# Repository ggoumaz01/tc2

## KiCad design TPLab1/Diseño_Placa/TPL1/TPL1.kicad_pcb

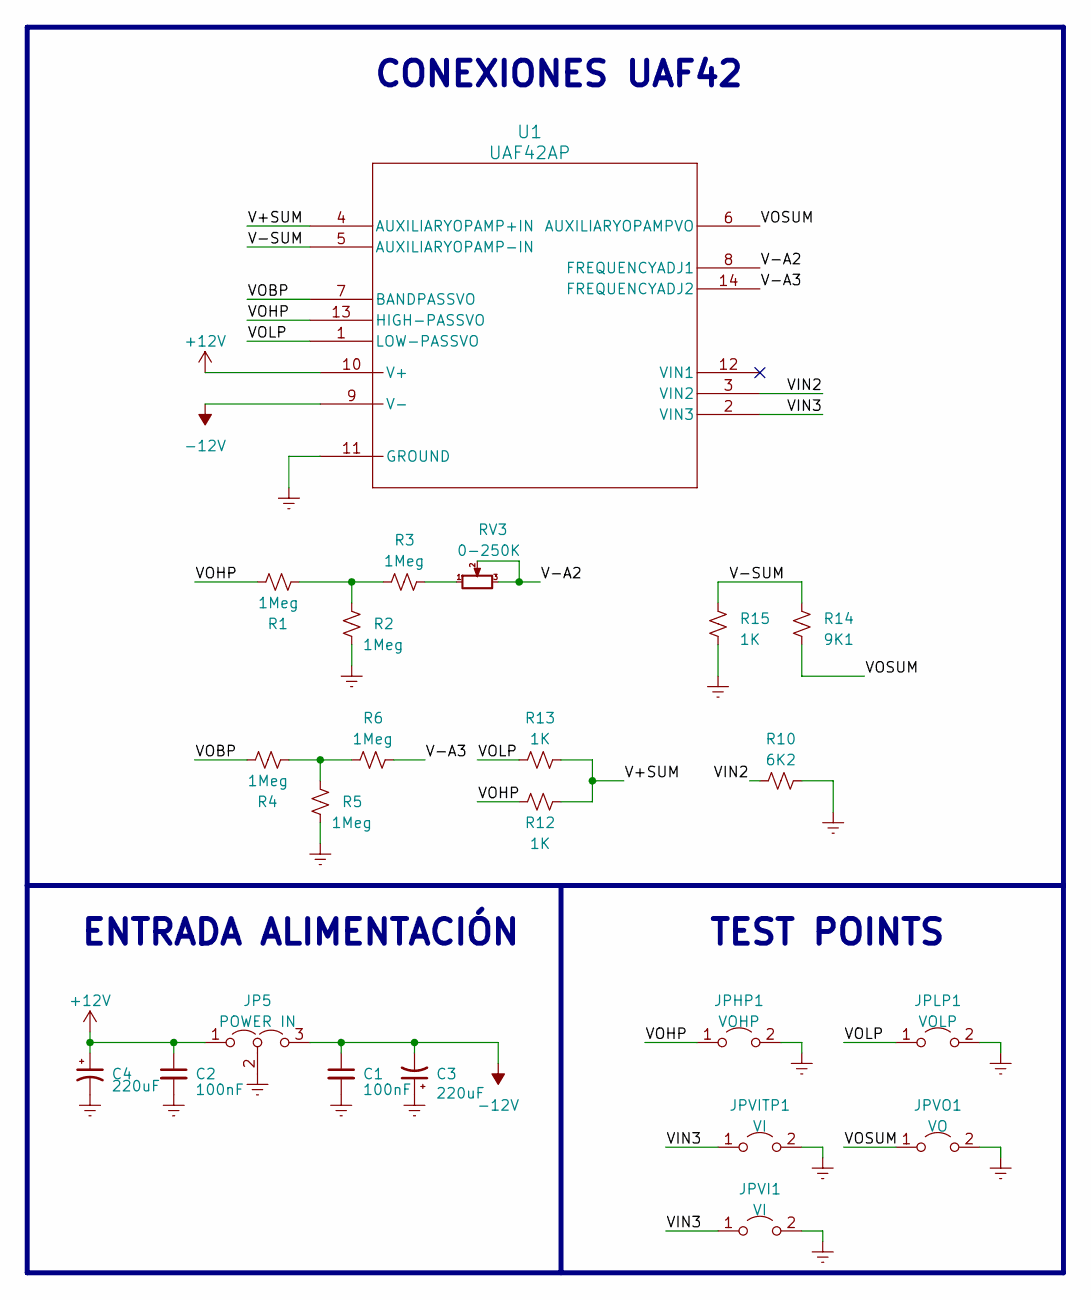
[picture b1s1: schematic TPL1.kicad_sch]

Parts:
C1, C2: 100nF; C_Disc_D3.0mm_W2.0mm_P2.50mm
C3, C4: 220uF; CP_Radial_D10.0mm_P2.50mm
JP5: POWER IN; TerminalBlock_bornier-3_P5.08mm
JPHP1: VOHP; PinHeader_1x02_P2.54mm_Vertical
JPLP1: VOLP; PinHeader_1x02_P2.54mm_Vertical
JPVI1: VI; PinHeader_1x02_P2.54mm_Vertical
JPVITP1: VI; PinHeader_1x02_P2.54mm_Vertical
JPVO1: VO; PinHeader_1x02_P2.54mm_Vertical
R1, R2, R3, R4, R5, R6: 1Meg; R_Axial_DIN0207_L6.3mm_D2.5mm_P7.62mm_Horizontal
R10: 6K2; R_Axial_DIN0207_L6.3mm_D2.5mm_P7.62mm_Horizontal
R12, R13, R15: 1K; R_Axial_DIN0207_L6.3mm_D2.5mm_P7.62mm_Horizontal
R14: 9K1; R_Axial_DIN0207_L6.3mm_D2.5mm_P7.62mm_Horizontal
RV3: 0-250K; Potentiometer_Bourns_3296W_Vertical
U1: UAF42AP; N14

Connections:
+12V: C2.1, C4.1, JP5.1 (A), U1.10 (V+)
-12V: C1.1, C3.2, JP5.3 (B), U1.9 (V-)
/V+SUM: R12.1, R13.2, U1.4 (AUXILIARYOPAMP+IN)
/V-A2: RV3.2, RV3.3, U1.8 (FREQUENCYADJ1)
/V-A3: R6.1, U1.14 (FREQUENCYADJ2)
/V-SUM: R14.2, R15.2, U1.5 (AUXILIARYOPAMP-IN)
/VIN2: R10.1, U1.3 (VIN2)
/VIN3: JPVI1.1 (A), JPVITP1.1 (A), U1.2 (VIN3)
/VOBP: R4.1, U1.7 (BANDPASSVO)
/VOHP: JPHP1.1 (A), R1.1, R12.2, U1.13 (HIGH-PASSVO)
/VOLP: JPLP1.1 (A), R13.1, U1.1 (LOW-PASSVO)
/VOSUM: JPVO1.1 (A), R14.1, U1.6 (AUXILIARYOPAMPVO)
Earth: C1.2, C2.2, C3.1, C4.2, JP5.2 (C), JPHP1.2 (B), JPLP1.2 (B), JPVI1.2 (B), JPVITP1.2 (B), JPVO1.2 (B), R2.2, R5.2, R10.2, R15.1, U1.11 (GROUND)
unnamed: R1.2, R2.1, R3.2
unnamed: R3.1, RV3.1
unnamed: R4.2, R5.1, R6.2

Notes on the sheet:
ENTRADA ALIMENTACIÓN
CONEXIONES UAF42
TEST POINTS

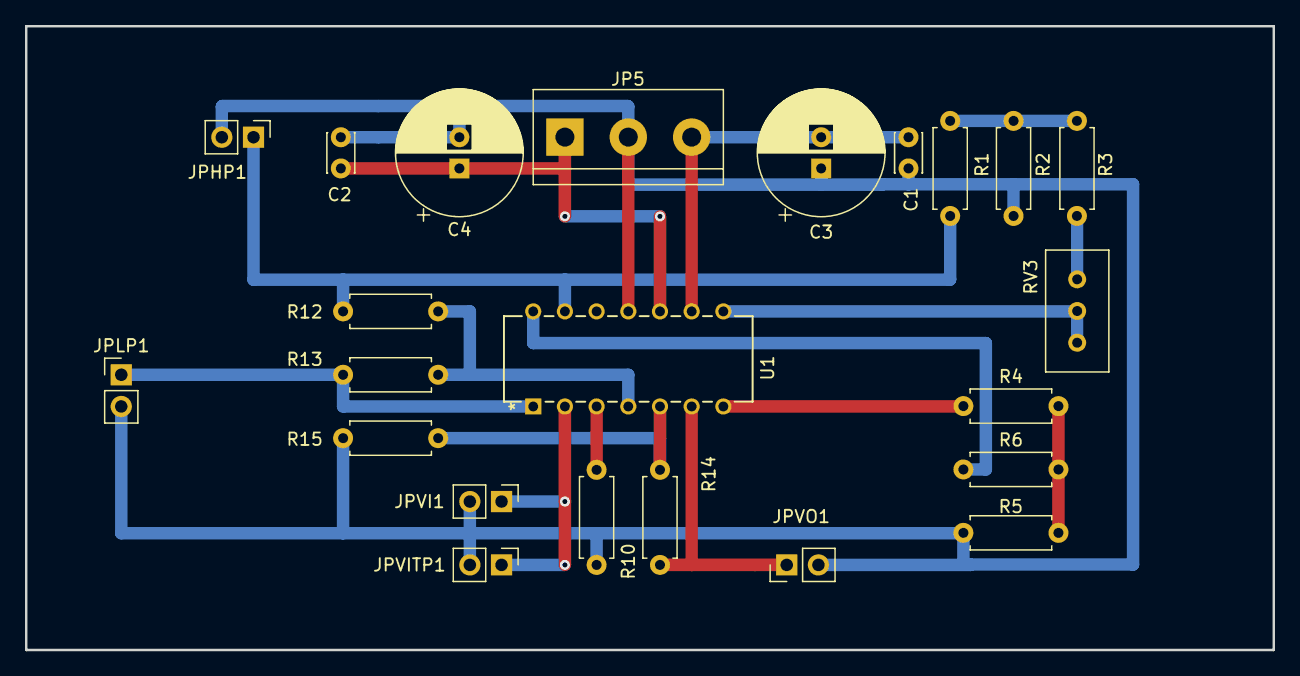
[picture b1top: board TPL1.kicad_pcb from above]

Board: 2 copper layers, 100.0 x 50.0 mm, 23 parts (0 on the bottom side), 16 nets.

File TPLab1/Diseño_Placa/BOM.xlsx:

# | Reference | Qty | Value
1 | C1, C2 | 2 | 100nF
2 | C3, C4 | 2 | 220uF
3 | JP5 | 1 | Bornera triple
4 | JPHP1, JPLP1, JPVI1, JPVITP1, JPVO1 | 5 | Pinera macho x2
5 | R1, R2, R3, R4, R5, R6 | 6 | 1Meg
6 | R10 | 1 | 6K2
7 | R12, R13, R15 | 3 | 1K
8 | R14 | 1 | 9K1
9 | RV3 | 1 | 0-250K
10 | U1 | 1 | UAF42AP
